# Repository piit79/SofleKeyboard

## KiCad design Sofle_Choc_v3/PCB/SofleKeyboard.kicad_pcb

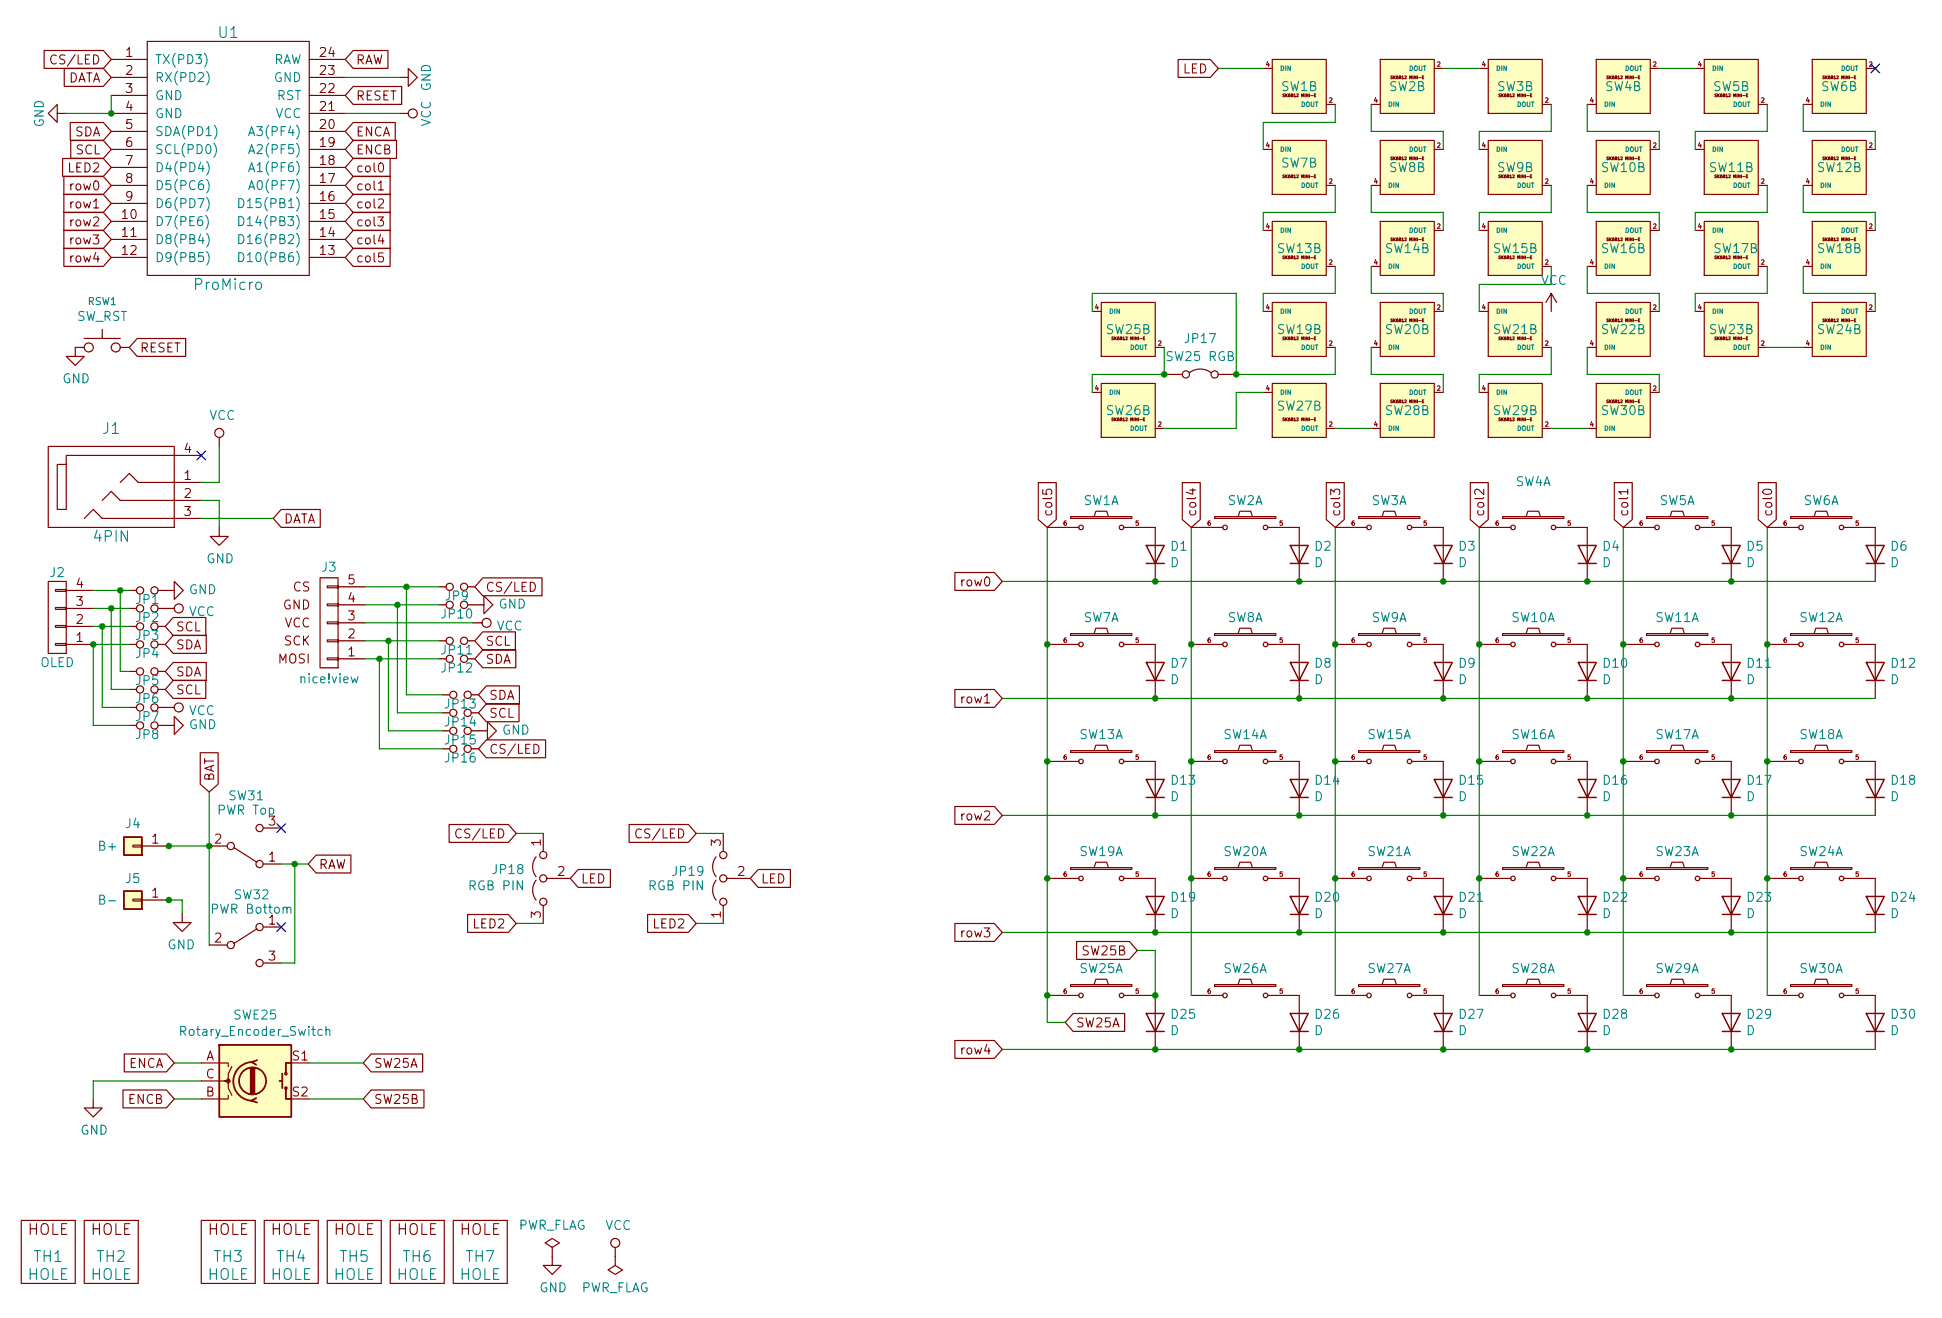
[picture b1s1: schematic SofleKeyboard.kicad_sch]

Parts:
D1, D2, D3, D4, D5, D6, D7, D8, D9, D10, D11, D12, D13, D14, D15, D16, D17, D18, D19, D20, D21, D22, D23, D24, D25, D26, D27, D28, D29, D30: D; SOD-123_with_cutout
J1: 4PIN; PJ-320A_double_sided_with_cutouts
J2: OLED; OLED_4Pin_with_cutouts
J3: nice!view; niceview_5Pin_with_cutouts
J4: B+; PinHeader_1x01_P2.54mm_Vertical_B+
J5: B-; PinHeader_1x01_P2.54mm_Vertical_B-
JP1, JP2, JP3, JP4, JP5, JP6, JP7, JP8, JP9, JP10, JP11, JP12, JP13, JP14, JP15, JP16: Jumper_NO_Small; Jumper
JP17: SW25 RGB; SolderJumper-2_P1.3mm_Bridged_RoundedPad1.0x1.5mm
JP18, JP19: RGB PIN; SolderJumper-3_P1.3mm_Open_RoundedPad1.0x1.5mm
RSW1: SW_RST; TACT_SWITCH_TVBP06_with_cutouts
SW1, SW2, SW3, SW4, SW5, SW6, SW7, SW8, SW9, SW10, SW11, SW12, SW13, SW14, SW15, SW16, SW17, SW18, SW19, SW20, SW21, SW22, SW23, SW24, SW26, SW27, SW28, SW29, SW30: SW_PUSH_LED; Choc_Hotswap_SK6812MiniE_with_cutouts
SW25: SW_PUSH_LED; Choc_Hotswap_SK6812MiniE_alt_pads_w_cutouts
SW31: PWR Top; SW_SPDT_PCM12
SW32: PWR Bottom; SW_SPDT_PCM12
SWE25: Rotary_Encoder_Switch; RotaryEncoder_Alps_EC11E-Switch_Vertical_H20mm-keebio_modif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
TH1, TH2: HOLE; MountingHole_2.2mm_M2_ISO7380_Pad
TH3, TH4, TH5, TH6, TH7: HOLE; HOLE_M2_TH_Smaller
U1: ProMicro; ProMicro_with_cutouts

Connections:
BAT: J4.1, SW31.2 (B), SW32.2 (B)
CS/LED: JP9.2, JP16.2, JP18.1 (A), JP19.3 (B), U1.1 (TX(PD3))
DATA: J1.3, U1.2 (RX(PD2))
ENCA: SWE25.A, U1.20 (A3(PF4))
ENCB: SWE25.B, U1.19 (A2(PF5))
GND: J1.2, J5.1, JP1.2, JP8.2, JP10.2, JP15.2, RSW1.1, SW1.3 (GND), SW2.3 (GND), SW3.3 (GND), SW4.3 (GND), SW5.3 (GND), SW6.3 (GND), SW7.3 (GND), SW8.3 (GND), SW9.3 (GND), SW10.3 (GND), SW11.3 (GND), SW12.3 (GND), SW13.3 (GND), SW14.3 (GND), SW15.3 (GND), SW16.3 (GND), SW17.3 (GND), SW18.3 (GND), SW19.3 (GND), SW20.3 (GND), SW21.3 (GND), SW22.3 (GND), SW23.3 (GND), SW24.3 (GND), SW25.3 (GND), SW26.3 (GND), SW27.3 (GND), SW28.3 (GND), SW29.3 (GND), SW30.3 (GND), SWE25.C, U1.3 (GND), U1.4 (GND), U1.23 (GND)
LED: JP18.2 (C), JP19.2 (C), SW1.4 (DIN)
LED2: JP18.3 (B), JP19.1 (A), U1.7 (D4(PD4))
unnamed: D1.2 (A), SW1.5
unnamed: D2.2 (A), SW2.5
unnamed: D3.2 (A), SW3.5
unnamed: D4.2 (A), SW4.5
unnamed: D5.2 (A), SW5.5
unnamed: D6.2 (A), SW6.5
unnamed: D7.2 (A), SW7.5
unnamed: D8.2 (A), SW8.5
unnamed: D9.2 (A), SW9.5
unnamed: D10.2 (A), SW10.5
unnamed: D11.2 (A), SW11.5
unnamed: D12.2 (A), SW12.5
unnamed: D13.2 (A), SW13.5
unnamed: D14.2 (A), SW14.5
unnamed: D15.2 (A), SW15.5
unnamed: D16.2 (A), SW16.5
unnamed: D17.2 (A), SW17.5
unnamed: D18.2 (A), SW18.5
unnamed: D19.2 (A), SW19.5
unnamed: D20.2 (A), SW20.5
unnamed: D21.2 (A), SW21.5
unnamed: D22.2 (A), SW22.5
unnamed: D23.2 (A), SW23.5
unnamed: D24.2 (A), SW24.5
unnamed: D26.2 (A), SW26.5
unnamed: D27.2 (A), SW27.5
unnamed: D28.2 (A), SW28.5
unnamed: D29.2 (A), SW29.5
unnamed: D30.2 (A), SW30.5
unnamed: J2.1, JP4.1, JP8.1
unnamed: J2.2, JP3.1, JP7.1
unnamed: J2.3, JP2.1, JP6.1
unnamed: J2.4, JP1.1, JP5.1
unnamed: J3.1, JP12.1, JP16.1
unnamed: J3.2, JP11.1, JP15.1
unnamed: J3.4, JP10.1, JP14.1
unnamed: J3.5, JP9.1, JP13.1
unnamed: JP17.1 (A), SW25.2 (DOUT), SW26.4 (DIN)
unnamed: JP17.2 (B), SW19.2 (DOUT), SW25.4 (DIN)
unnamed: SW1.2 (DOUT), SW7.4 (DIN)
unnamed: SW2.4 (DIN), SW8.2 (DOUT)
unnamed: SW2.2 (DOUT), SW3.4 (DIN)
unnamed: SW3.2 (DOUT), SW9.4 (DIN)
unnamed: SW4.2 (DOUT), SW5.4 (DIN)
unnamed: SW10.4 (DIN), SW16.2 (DOUT)
unnamed: SW4.4 (DIN), SW10.2 (DOUT)
unnamed: SW5.2 (DOUT), SW11.4 (DIN)
unnamed: SW11.2 (DOUT), SW17.4 (DIN)
unnamed: SW12.4 (DIN), SW18.2 (DOUT)
unnamed: SW6.4 (DIN), SW12.2 (DOUT)
unnamed: SW7.2 (DOUT), SW13.4 (DIN)
unnamed: SW13.2 (DOUT), SW19.4 (DIN)
unnamed: SW14.4 (DIN), SW20.2 (DOUT)
unnamed: SW8.4 (DIN), SW14.2 (DOUT)
unnamed: SW9.2 (DOUT), SW15.4 (DIN)
unnamed: SW15.2 (DOUT), SW21.4 (DIN)
unnamed: SW16.4 (DIN), SW22.2 (DOUT)
unnamed: SW17.2 (DOUT), SW23.4 (DIN)
unnamed: SW18.4 (DIN), SW24.2 (DOUT)
unnamed: SW20.4 (DIN), SW28.2 (DOUT)
unnamed: SW21.2 (DOUT), SW29.4 (DIN)
unnamed: SW22.4 (DIN), SW30.2 (DOUT)
unnamed: SW23.2 (DOUT), SW24.4 (DIN)
unnamed: SW26.2 (DOUT), SW27.4 (DIN)
unnamed: SW27.2 (DOUT), SW28.4 (DIN)
unnamed: SW29.2 (DOUT), SW30.4 (DIN)
RAW: SW31.1 (A), SW32.3 (C), U1.24 (RAW)
RESET: RSW1.2, U1.22 (RST)
SCL: JP3.2, JP6.2, JP11.2, JP14.2, U1.6 (SCL(PD0))
SDA: JP4.2, JP5.2, JP12.2, JP13.2, U1.5 (SDA(PD1))
SW25A: SW1.6, SW7.6, SW13.6, SW19.6, SW25.6, SWE25.S1, U1.13 (D10(PB6))
SW25B: D25.2 (A), SW25.5, SWE25.S2
VCC: J1.1, J3.3, JP2.2, JP7.2, SW1.1 (VDD), SW2.1 (VDD), SW3.1 (VDD), SW4.1 (VDD), SW5.1 (VDD), SW6.1 (VDD), SW7.1 (VDD), SW8.1 (VDD), SW9.1 (VDD), SW10.1 (VDD), SW11.1 (VDD), SW12.1 (VDD), SW13.1 (VDD), SW14.1 (VDD), SW15.1 (VDD), SW16.1 (VDD), SW17.1 (VDD), SW18.1 (VDD), SW19.1 (VDD), SW20.1 (VDD), SW21.1 (VDD), SW22.1 (VDD), SW23.1 (VDD), SW24.1 (VDD), SW25.1 (VDD), SW26.1 (VDD), SW27.1 (VDD), SW28.1 (VDD), SW29.1 (VDD), SW30.1 (VDD), U1.21 (VCC)
col0: SW6.6, SW12.6, SW18.6, SW24.6, SW30.6, U1.18 (A1(PF6))
col1: SW5.6, SW11.6, SW17.6, SW23.6, SW29.6, U1.17 (A0(PF7))
col2: SW4.6, SW10.6, SW16.6, SW22.6, SW28.6, U1.16 (D15(PB1))
col3: SW3.6, SW9.6, SW15.6, SW21.6, SW27.6, U1.15 (D14(PB3))
col4: SW2.6, SW8.6, SW14.6, SW20.6, SW26.6, U1.14 (D16(PB2))
row0: D1.1 (K), D2.1 (K), D3.1 (K), D4.1 (K), D5.1 (K), D6.1 (K), U1.8 (D5(PC6))
row1: D7.1 (K), D8.1 (K), D9.1 (K), D10.1 (K), D11.1 (K), D12.1 (K), U1.9 (D6(PD7))
row2: D13.1 (K), D14.1 (K), D15.1 (K), D16.1 (K), D17.1 (K), D18.1 (K), U1.10 (D7(PE6))
row3: D19.1 (K), D20.1 (K), D21.1 (K), D22.1 (K), D23.1 (K), D24.1 (K), U1.11 (D8(PB4))
row4: D25.1 (K), D26.1 (K), D27.1 (K), D28.1 (K), D29.1 (K), D30.1 (K), U1.12 (D9(PB5))

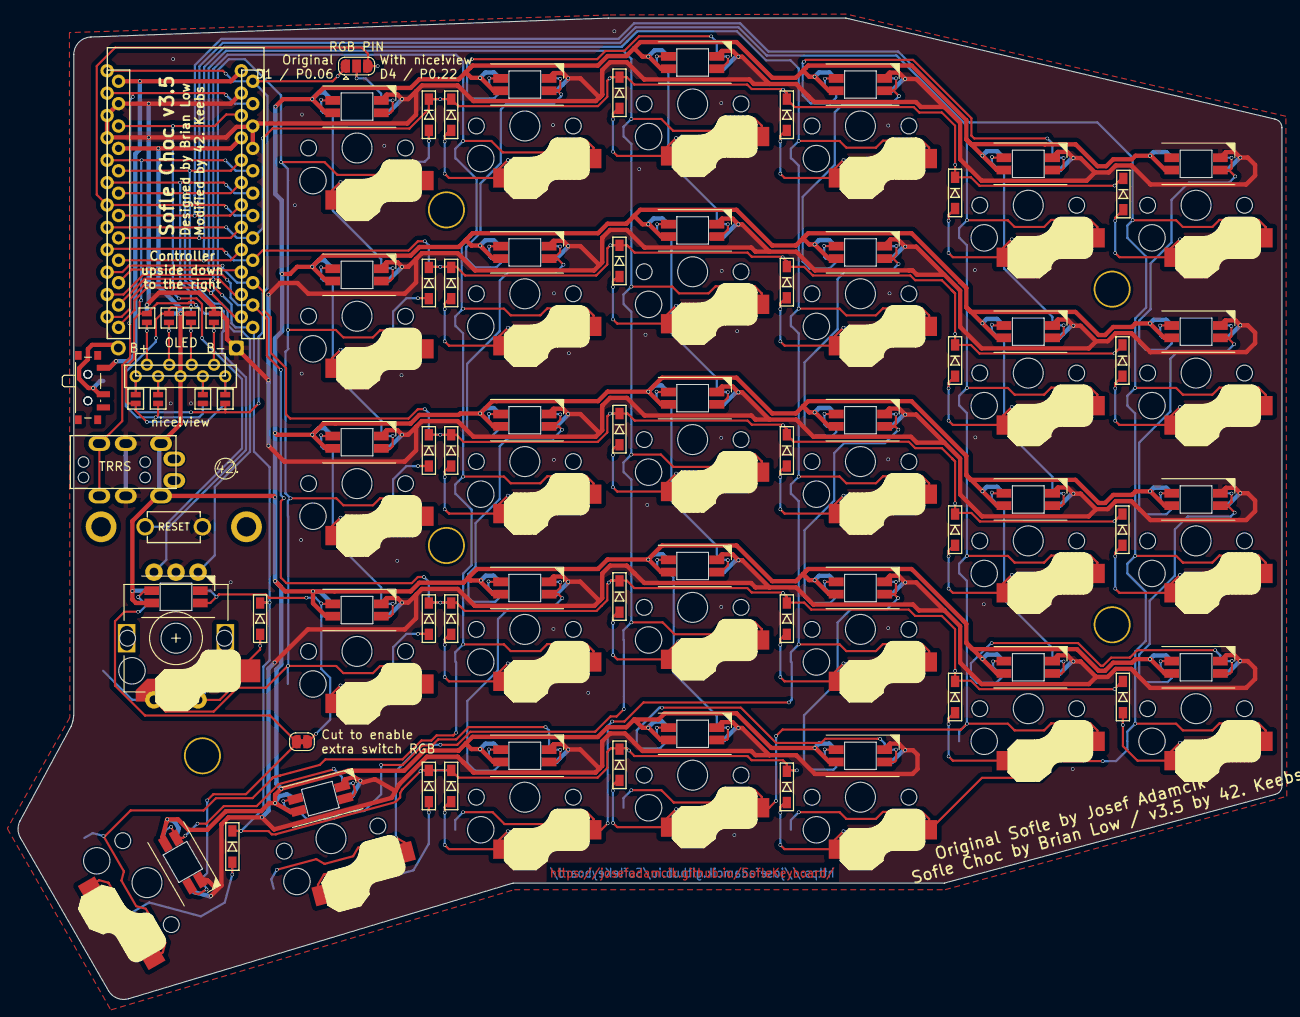
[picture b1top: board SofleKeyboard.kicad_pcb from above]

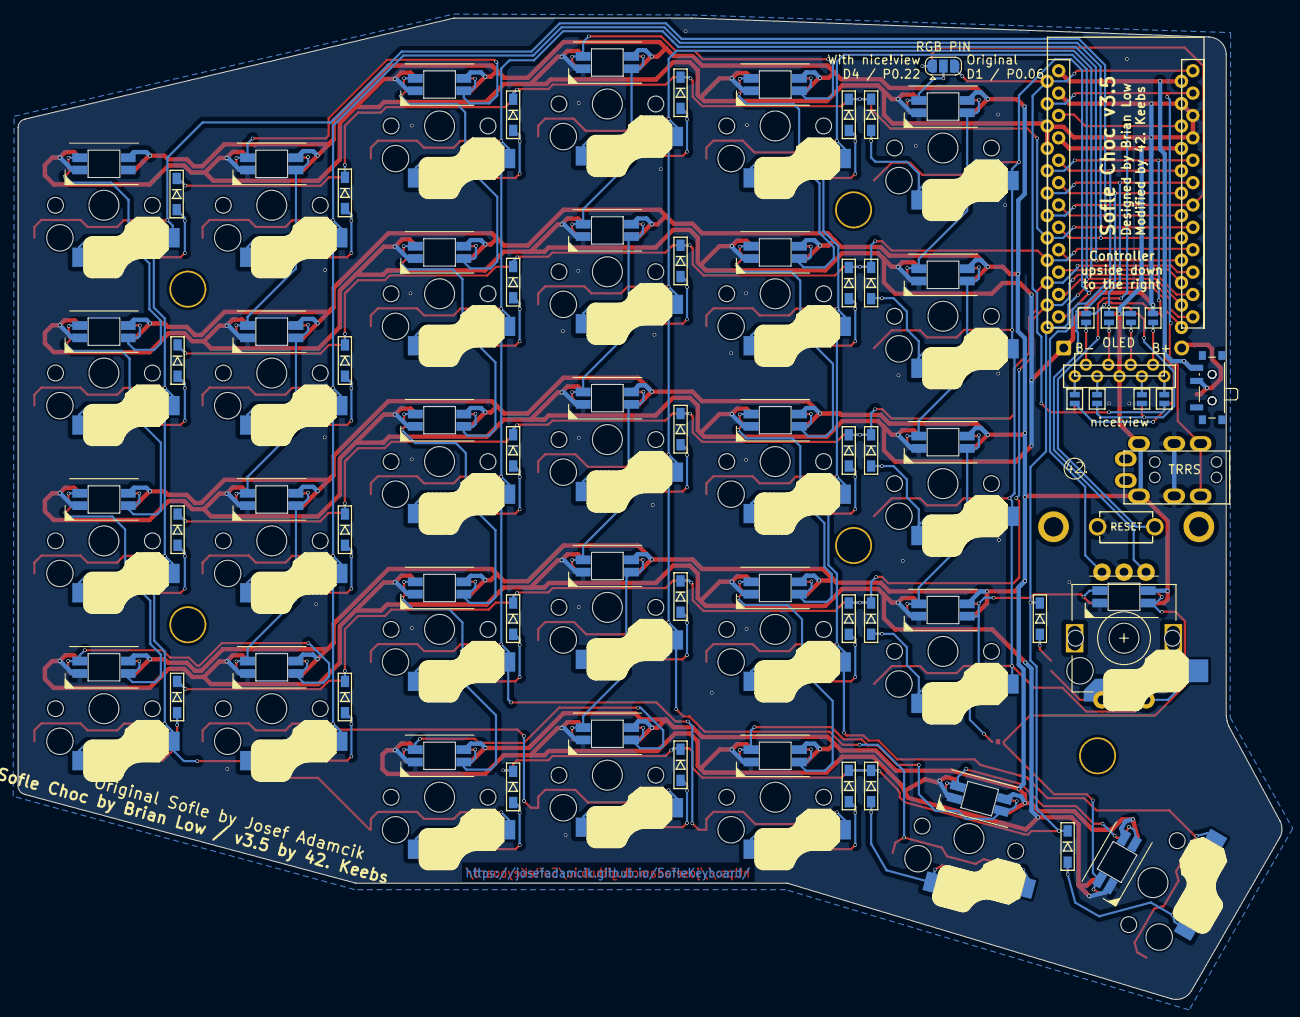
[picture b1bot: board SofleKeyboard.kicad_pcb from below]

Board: 2 copper layers, 143.5 x 111.4 mm, 96 parts (10 on the bottom side), 91 nets.

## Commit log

2023-02-07 Add Sofle Choc v2.2 with power switch, battery footprint and modified outline
2023-02-07 Add Sofle RGB 'v3' variant with Sofle v2 pinky stagger
2023-02-28 Sofle Choc v2.2.1: reverse power switch direction (up - on); add gerbers
2024-06-01 Add Sofle Choc v3 variant with Sofle v2 pinky stagger
    Also includes native nice!view support, power switch and battery contacts
2024-08-07 Sofle RGB V3.2 with native nice!view support
2024-08-07 Update Sofle RGB V3 plates
2024-08-11 Add various footprints with cutouts
2024-08-11 Sofle RGB V3.4
    * Fix missing connection between underglow and backlight
2024-12-06 Add Sofle Choc v3 acrylic switch and bottom plates
2024-12-06 Add Sofle Choc v3.3 gerbers
2024-12-06 Add Sofle Choc v3 switch plate
2024-12-06 Update Sofle Choc v3.5 gerbers
2024-12-06 Sofle Choc: add support for extra switch instead of encoder
2024-12-11 Update the case for Sofle RGB V3
    Includes partial and full sandwich cases
    in standard and tenting versions
2024-12-11 Update gerbers for the Sofle RGB V3
